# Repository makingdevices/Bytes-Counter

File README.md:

<!-- Improved compatibility of back to top link: See: https://github.com/othneildrew/Best-README-Template/pull/73 -->

<!--
*** Thanks for checking out the Best-README-Template. If you have a suggestion
*** that would make this better, please fork the repo and create a pull request
*** or simply open an issue with the tag "enhancement".
*** Don't forget to give the project a star!
*** Thanks again! Now go create something AMAZING! :D
-->

<!-- PROJECT SHIELDS -->
<!--
*** I'm using markdown "reference style" links for readability.
*** Reference links are enclosed in brackets [ ] instead of parentheses ( ).
*** See the bottom of this document for the declaration of the reference variables
*** for contributors-url, forks-url, etc. This is an optional, concise syntax you may use.
*** https://www.markdownguide.org/basic-syntax/#reference-style-links
-->
[![Instagram][ig-shield]][ig-url]
[![PCBWAY][sponsor-shield]][sponsor-url]
[![Stargazers][stars-shield]][stars-url]
[![Issues][issues-shield]][issues-url]
[![LinkedIn][linkedin-shield]][linkedin-url]

<!-- PROJECT LOGO -->
<br />
<div align="center">

<h3 align="center">Making Devices</h3>

  <p align="center">
    Open Source projects where we struggle with engineering, electronics, coding and who knows what else... In this case, Bytes Counter is a very simple digital tally counter, so hopefully you may find it interesting ;)
  </p>
</div>

<!-- TABLE OF CONTENTS -->
<details>
  <summary>Table of Contents</summary>
  <ol>
    <li>
      <a href="#about-the-project">About The Project</a>
      <ul>
        <li><a href="#built-with">Built With</a></li>
      </ul>
    </li>
    <li>
      <a href="#Build-one">Build one</a>
      <ul>
      </ul>
    </li>
    <li><a href="#usage">Usage</a></li>
    <li><a href="#roadmap">Roadmap</a></li>
    <li><a href="#license">License</a></li>
    <li><a href="#contact">Contact</a></li>
    <li><a href="#Sponsor">Sponsor</a></li>
  </ol>
</details>

<!-- ABOUT THE PROJECT -->
## About The Project

[![Bytes Counter Shot][product-screenshot]](https://makingdevices.com/Bytes-Counter)

Bytes Counter is a simple Tally Counter for counting people in places, helping you in inventories, practising soldering or just counting things at work! The project was chosen to test some PCB manufacturer capabilities and experiment with both the XLP (Extreme Low-Power Technology) and the pic18LF14k50 itself

The PCB does not have any power button, since the project's approach is to use the XLP technology of the PIC. It only has two buttons: increase/decrease the count.

A buzzer helps you count anything without needing to read the display every time so that you can focus on your work.

Even after weeks or months, the count is kept while in deep sleep mode.

<p align="right">(<a href="#readme-top">back to top</a>)</p>

### Built With

[![Microcontroller][PIC]][PIC-url]
[![MPLAB C][MPLAB-C]][MPLAB-C-url]
[![Kicad][kicad-shield]][kicad-url]
[![SPONSOR][sponsor-icon]][sponsor-url]

<p align="right">(<a href="#readme-top">back to top</a>)</p>

<!-- GETTING STARTED -->

## Build one

1. Get the gerber files for the latest version: [V1](https://github.com/makingdevices/Bytes-Counter/blob/main/v1/Gerber/BytesCounterV1.zip) 
2. Send them to a PCB manufacturer ([Our Sponsor is PCBWAY][sponsor-url])
3. Buy all the components from the [Bill Of Materials](https://github.com/makingdevices/Bytes-Counter/blob/main/v1/BytesCounter_BOM.xlsx)
4. Solder everything with the help of the [schematic](https://github.com/makingdevices/Bytes-Counter/blob/main/v1/schematicv1.pdf)
5. Burn the [latest firmware](https://github.com/makingdevices/Bytes-Counter/blob/main/v1/Simulation/Bytes_Counter.hex)
6. Give us a Star to the respository ;)

Here it is an assembly video:

[![Assembly Shot][YT-screenshot]](https://www.youtube.com/watch?v=Gu0cR_CFLYs)

<p align="right">(<a href="#readme-top">back to top</a>)</p>

<!-- USAGE EXAMPLES -->
## Usage

Instructions of use:

- Pressing "+" or "-" will increase/decrease the count.
- Long press "+" : Sound Event -> Activate/Deactivate buzzer sounds.
- Long press "-" : Reset event -> Reset the count.
- 60s without pressing any button: Deep Sleep Mode -> Display off.
- Any button pulsation will exit Deep Sleep Mode.

<p align="right">(<a href="#readme-top">back to top</a>)</p>

<!-- ROADMAP -->
## Roadmap

- [x] Count up/down and show it on screen
- [x] enable/disable sound when pressing buttons
- [x] Low Power Consumption
    - [x] Lower the frequency of the microcontroller at minimum
    - [x] Enter deep sleep mode automatically

See the [open issues](https://github.com/makingdevices/Bytes-Counter/issues) for a full list of proposed features (and known issues).

State: Project <b>FINISHED</b> - 01/08/2022

<p align="right">(<a href="#readme-top">back to top</a>)</p>

<!-- LICENSE -->
## License

Distributed under three licenses:
- [Hardware](/License/HW_cern_ohl_s_v2.pdf)
- [Software](/License/SW_GPLv3.0.txt)
- [Documentation](/License/Documentation_CC-BY-SA-4.0.txt)

[![GPL v3 License][license-shield]][license-url] 
<p align="right">(<a href="#readme-top">back to top</a>)</p>

<!-- CONTACT -->
## Contact

Making Devices - [@MakingDevices](https://www.instagram.com/makingdevices/)

Project Link: [https://github.com/makingdevices/Bytes-Counter](https://github.com/makingdevices/Bytes-Counter)

Other Links: [LinkTree](https://makingdevices.com/links/)

<p align="right">(<a href="#readme-top">back to top</a>)</p>

<!-- Sponsor -->
## Sponsor

[PCBWAY](https://www.pcbway.com/?from=makingdevices) helped us with the fabrication of the PCBs. You can check their quality with the following pictures:

[![PCB Shot 1][pcb_pic1]](https://www.pcbway.com/?from=makingdevices)
[![PCB Shot 2][pcb_pic2]](https://www.pcbway.com/?from=makingdevices)

Should you want to colaborate with MakingDevices, you can buy a [BytesCounter fully assembled and ready to use](https://www.pcbway.com/project/gifts_detail/Bytes_Counter_v1_0_4c88cb45.html) ;).

<p align="right">(<a href="#readme-top">back to top</a>)</p>

<!-- MARKDOWN LINKS & IMAGES -->
<!-- https://www.markdownguide.org/basic-syntax/#reference-style-links -->
[contributors-shield]: https://img.shields.io/github/contributors/makingdevices/Bytes-Counter.svg?style=for-the-badge
[contributors-url]: https://github.com/makingdevices/Bytes-Counter/graphs/contributors
[forks-shield]: https://img.shields.io/github/forks/makingdevices/Bytes-Counter.svg?style=for-the-badge
[forks-url]: https://github.com/makingdevices/Bytes-Counter/network/members
[stars-shield]: https://img.shields.io/github/stars/makingdevices/Bytes-Counter.svg?style=for-the-badge
[stars-url]: https://github.com/makingdevices/Bytes-Counter/stargazers
[issues-shield]: https://img.shields.io/github/issues/makingdevices/Bytes-Counter.svg?style=for-the-badge
[issues-url]: https://github.com/makingdevices/Bytes-Counter/issues
[license-shield]: /images/license.png
[license-url]: https://github.com/makingdevices/Bytes-Counter/tree/main/License
[linkedin-shield]: https://img.shields.io/badge/-LinkedIn-black.svg?style=for-the-badge&logo=linkedin&colorB=555
[linkedin-url]: https://www.linkedin.com/company/making-devices/
[sponsor-shield]: https://img.shields.io/badge/SPONSOR-PCBWAY-black.svg?style=for-the-badge&colorB=1200
[sponsor-url]: https://www.pcbway.com/?from=makingdevices
[sponsor-screenshot]: /images/PCB_sponsor.png
[product-screenshot]: images/screenshot.jpg
[pcb_pic1]: images/bytescounter_pcb_1.jpg
[pcb_pic2]: images/bytescounter_pcb_2.jpg
[PIC]: https://img.shields.io/badge/PIC18LF14K50-000000?style=for-the-badge
[PIC-url]: http://ww1.microchip.com/downloads/en/devicedoc/40001350f.pdf
[kicad-shield]: https://img.shields.io/badge/kicad-0b03fc?style=for-the-badge&logo=kicad&logoColor=white
[kicad-url]: https://www.kicad.org/
[YT-screenshot]: images/YT_assembly.PNG
[sponsor-icon]:  https://img.shields.io/badge/-PCBWAY-black.svg?style=for-the-badge&colorB=1200
[ig-shield]: https://img.shields.io/badge/instagram-a83297?style=for-the-badge&logo=instagram&logoColor=white
[ig-url]: https://www.instagram.com/makingdevices/
[MPLAB-C]: https://img.shields.io/badge/MPLAB%20C18-DD0031?style=for-the-badge&logo=C&logoColor=white
[MPLAB-C-url]: https://www.microchip.com/en-us/development-tool/SW006011
[Svelte.dev]: https://img.shields.io/badge/Svelte-4A4A55?style=for-the-badge&logo=svelte&logoColor=FF3E00
[Svelte-url]: https://svelte.dev/
[Laravel.com]: https://img.shields.io/badge/Laravel-FF2D20?style=for-the-badge&logo=laravel&logoColor=white
[Laravel-url]: https://laravel.com
[Bootstrap.com]: https://img.shields.io/badge/Bootstrap-563D7C?style=for-the-badge&logo=bootstrap&logoColor=white
[Bootstrap-url]: https://getbootstrap.com
[JQuery.com]: https://img.shields.io/badge/jQuery-0769AD?style=for-the-badge&logo=jquery&logoColor=white
[JQuery-url]: https://jquery.com

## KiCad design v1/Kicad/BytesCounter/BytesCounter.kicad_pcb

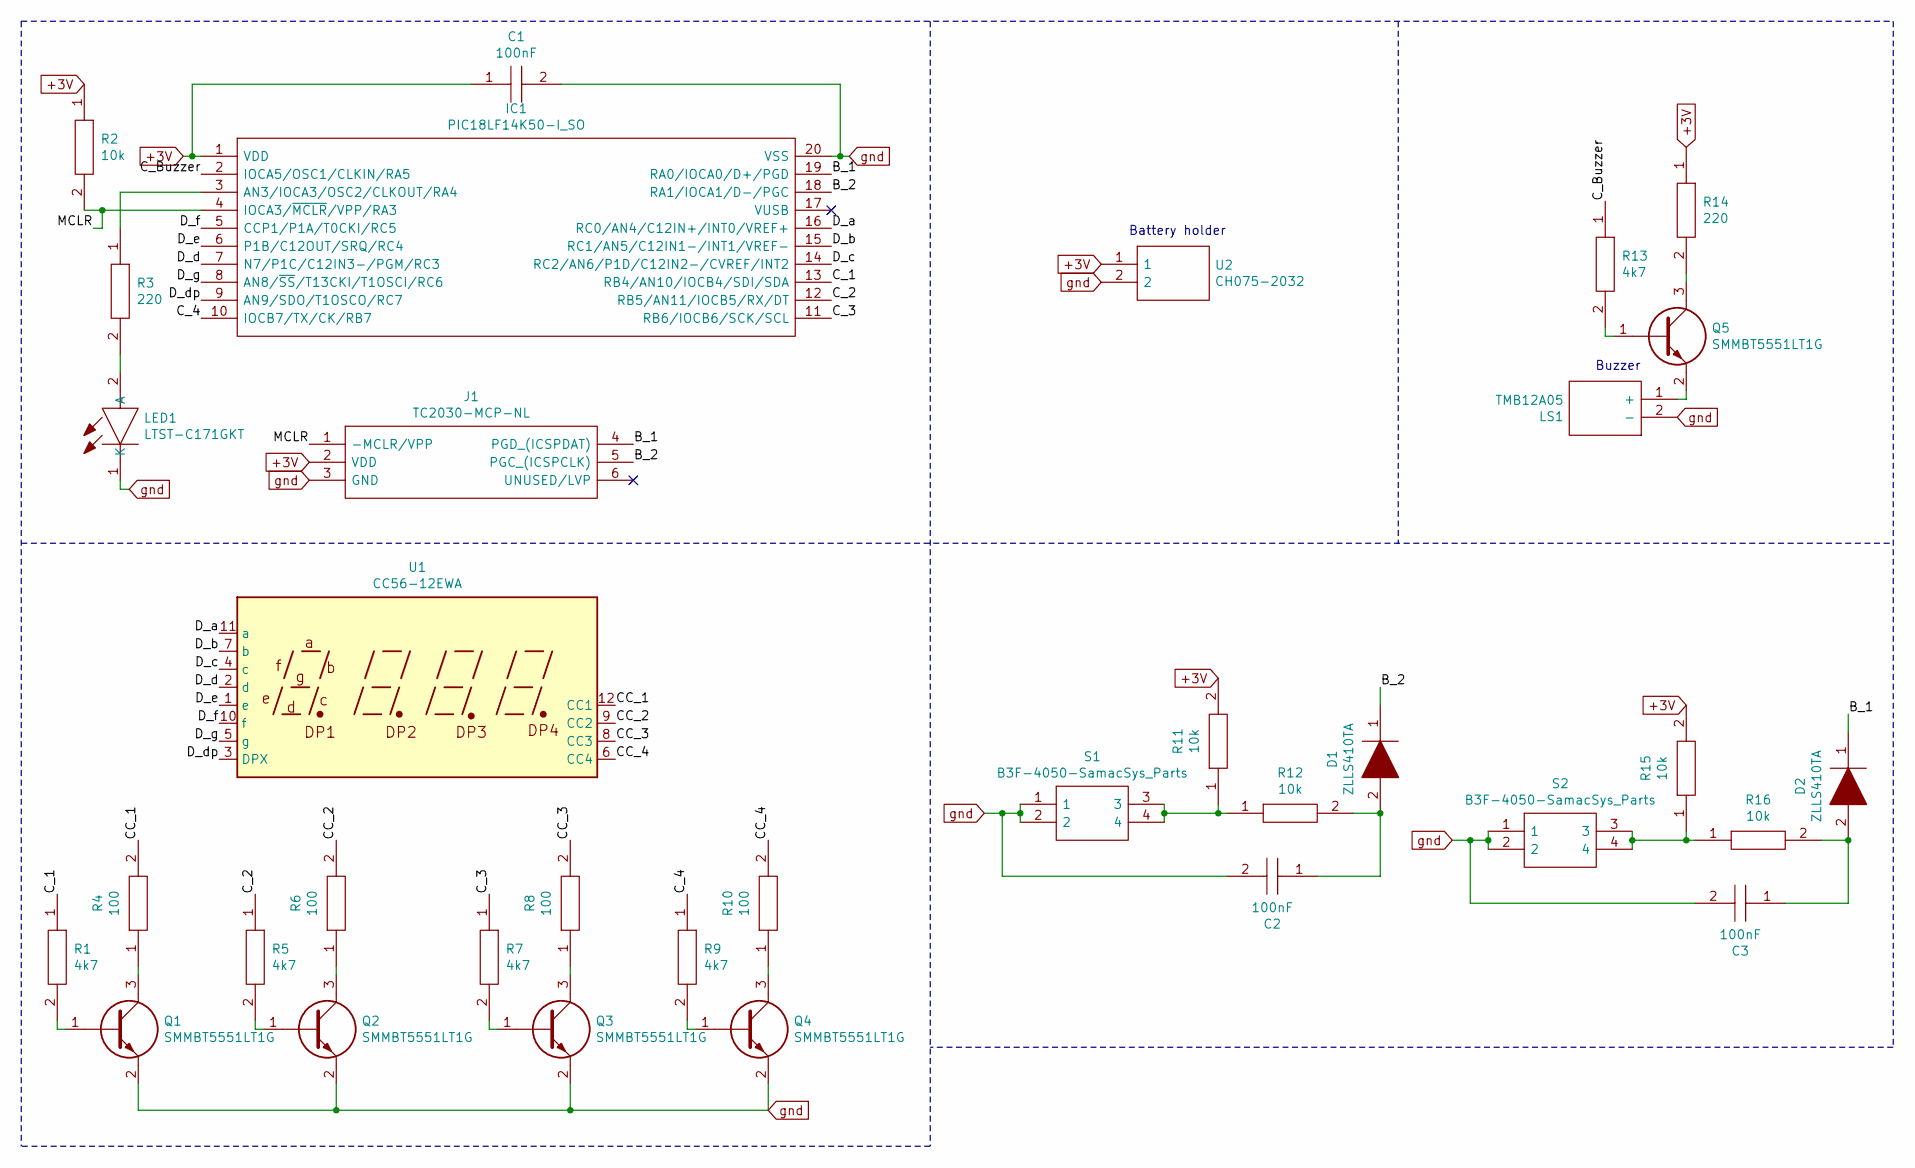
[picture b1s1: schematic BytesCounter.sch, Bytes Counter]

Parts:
C1, C2, C3: 100nF; CAPC2012X145N; Manufacturer_Part_Number GCG21BR71H154KA01K
D1, D2: ZLLS410TA; SOD2513X120N; Manufacturer_Part_Number ZLLS410TA
IC1: PIC18LF14K50-I_SO; SSOP-20_5.3x7.2mm_P0.65mm; Manufacturer_Part_Number PIC18LF14K50-I/SO
J1: TC2030-MCP-NL; Manufacturer_Part_Number TC2030-MCP-NL
LED1: LTST-C171GKT; LEDC2012X90N; Manufacturer_Part_Number LTST-C171GKT
LS1: TMB12A05; Manufacturer_Part_Number TMB12A05
Q1, Q2, Q3, Q4, Q5: SMMBT5551LT1G; SOT96P237X111-3N; Manufacturer_Part_Number SMMBT5551LT1G
R1, R5, R7, R9, R13: 4k7; RESC2012X65N; Manufacturer_Part_Number KTR10EZPF4220
R2, R11, R12, R15, R16: 10k; RESC2012X65N; Manufacturer_Part_Number KTR10EZPF4220
R3, R14: 220; RESC2012X65N; Manufacturer_Part_Number KTR10EZPF4220
R4, R6, R8, R10: 100; RESC2012X65N; Manufacturer_Part_Number KTR10EZPF4220
S1, S2: B3F-4050-SamacSys_Parts; B3F-4000; Manufacturer_Part_Number B3F-4050; Mouser Part Number 653-B3F-4050
U1: CC56-12EWA; CA56-12EWA
U2: CH075-2032; CH0752032; Manufacturer_Part_Number CH075-2032

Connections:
+3V: C1.1, IC1.1 (VDD), J1.2 (VDD), R2.1, R11.2, R14.1, R15.2, U2.1
/B_1: D2.1, IC1.19 (RA0/IOCA0/D+/PGD), J1.4 (PGD_(ICSPDAT))
/B_2: D1.1, IC1.18 (RA1/IOCA1/D-/PGC), J1.5 (PGC_(ICSPCLK))
/CC_1: R4.2, U1.12 (CC1)
/CC_2: R6.2, U1.9 (CC2)
/CC_3: R8.2, U1.8 (CC3)
/CC_4: R10.2, U1.6 (CC4)
/C_1: IC1.13 (RB4/AN10/IOCB4/SDI/SDA), R1.1
/C_2: IC1.12 (RB5/AN11/IOCB5/RX/DT), R5.1
/C_3: IC1.11 (RB6/IOCB6/SCK/SCL), R7.1
/C_4: IC1.10 (IOCB7/TX/CK/RB7), R9.1
/C_Buzzer: IC1.2 (IOCA5/OSC1/CLKIN/RA5), R13.1
/D_a: IC1.16 (RC0/AN4/C12IN+/INT0/VREF+), U1.11 (a)
/D_b: IC1.15 (RC1/AN5/C12IN1-/INT1/VREF-), U1.7 (b)
/D_c: IC1.14 (RC2/AN6/P1D/C12IN2-/CVREF/INT2), U1.4 (c)
/D_d: IC1.7 (N7/P1C/C12IN3-/PGM/RC3), U1.2 (d)
/D_dp: IC1.9 (AN9/SDO/T1OSCO/RC7), U1.3 (DPX)
/D_e: IC1.6 (P1B/C12OUT/SRQ/RC4), U1.1 (e)
/D_f: IC1.5 (CCP1/P1A/T0CKI/RC5), U1.10 (f)
/D_g: IC1.8 (AN8/~SS~/T13CKI/T1OSCI/RC6), U1.5 (g)
/MCLR: IC1.4 (IOCA3/~MCLR~/VPP/RA3), J1.1 (-MCLR/VPP), R2.2
unnamed: C2.1, D1.2, R12.2
unnamed: C3.1, D2.2, R16.2
unnamed: IC1.3 (AN3/IOCA3/OSC2/CLKOUT/RA4), R3.1
unnamed: LED1.2 (A), R3.2
unnamed: LS1.1 (+), Q5.2
unnamed: Q1.1, R1.2
unnamed: Q1.3, R4.1
unnamed: Q2.1, R5.2
unnamed: Q2.3, R6.1
unnamed: Q3.1, R7.2
unnamed: Q3.3, R8.1
unnamed: Q4.1, R9.2
unnamed: Q4.3, R10.1
unnamed: Q5.1, R13.2
unnamed: Q5.3, R14.2
unnamed: R11.1, R12.1, S1.3, S1.4
unnamed: R15.1, R16.1, S2.3, S2.4
gnd: C1.2, C2.2, C3.2, IC1.20 (VSS), J1.3 (GND), LED1.1 (K), LS1.2 (-), Q1.2, Q2.2, Q3.2, Q4.2, S1.1, S1.2, S2.1, S2.2, U2.2

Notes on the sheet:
Battery holder
Buzzer

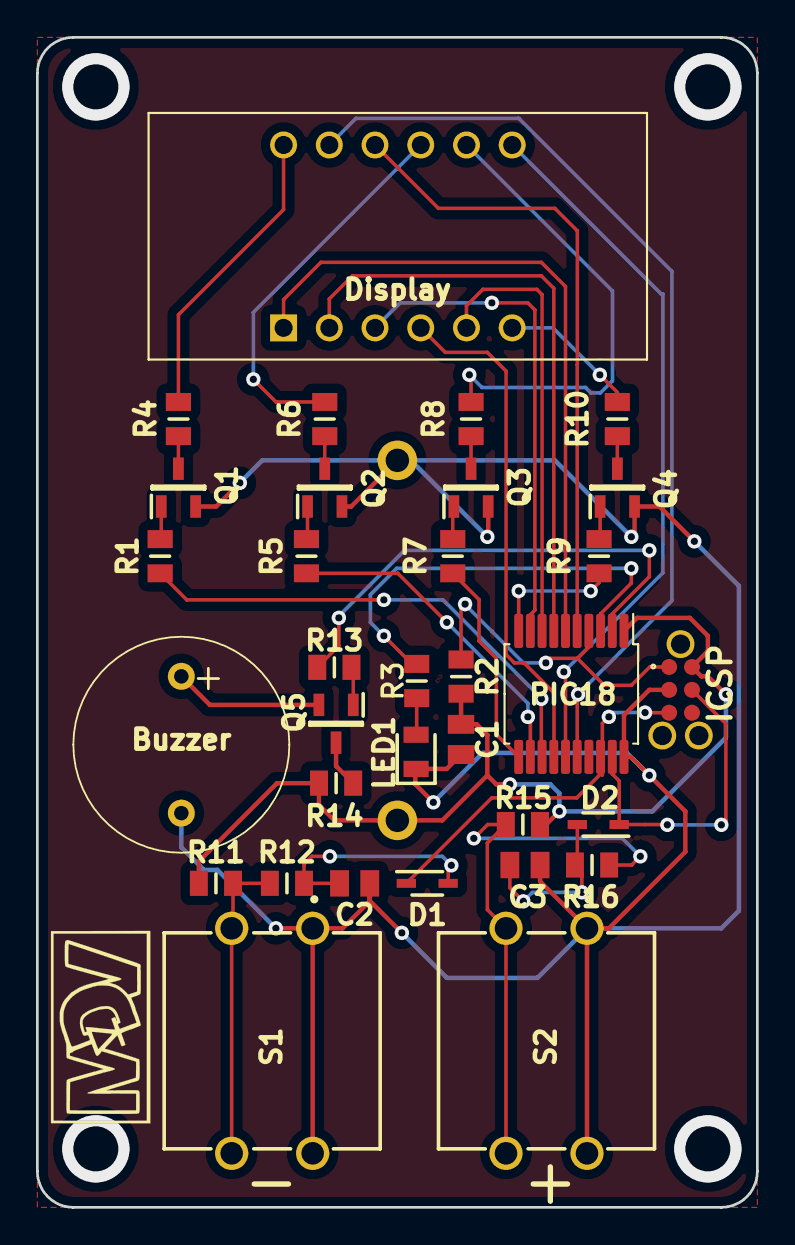
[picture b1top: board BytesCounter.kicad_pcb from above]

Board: 2 copper layers, 40.0 x 65.0 mm, 34 parts (1 on the bottom side), 39 nets.

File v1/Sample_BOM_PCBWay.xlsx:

|  |  |  | Bytes Counter v1 BOM (Sample Bill of Materials)
Item # | *Designator | *Qty | Layer | Manufacturer | *Mfg Part # | Description / Value | *Package/Footprint | Type | Your Instructions / Notes | Price
1 | IC1 | 1 | top | Microchip | PIC18LF14K50T-I/SS | MicroProcessor | 20-SSOP | SMD | It has to be the official part
2 | LED1 | 1 | top | TOGIALED | TJ-S2012SW8TGLC2G-A5 | Green LED | 0805 | SMD | It can be replaced for other parts
3 | Q1,Q2,Q3,Q4,Q5 | 5 | top | TOSHIBA | 2SC2712 | NPN transistor 150mA | SOT23-3 | SMD | It can be replaced for other parts
4 | R3, R14 | 2 | top | RALEC | RTT052200FTP | 220 Ohm Resistor / 125mW | 0805 | SMD | It can be replaced for other parts
5 | R4, R6, R8, R10 | 4 | top | YAGEO | RC0805FR-7W100RL | 100 Ohm Resistor / 250mW | 0805 | SMD | It can be replaced for other parts
6 | R1, R5, R7, R9, R13 | 5 | top | RALEC | RTT054701FTP | 4.7k Ohm Resistor / 125mW | 0805 | SMD | It can be replaced for other parts
7 | R2, R11, R12, R15, R16 | 5 | top | YAGEO | RT0805CRD0710KL | 10K Ohm Resistor / 125mW | 0805 | SMD | It can be replaced for other parts
8 | C1, C2, C3 | 3 | top | YAGEO | AC0805KRX7R9BB104 | 100nF Capacitor 50V | 0805 | SMD | It can be replaced for other parts
9 | D1, D2 | 2 | top | BAS170WS-E3-08 | Vishay Intertech | 70V Schottky diode | SOD-323-2 | SMD | It can be replaced for other parts
10 | S1, S2 | 2 | top | Diptronics | DTS-21K-V | Buttons | 4POS | thru-hole | It can be replaced for other parts
11 | U2 | 1 | Bottom | AAA-BAT-029-K01 | LOTES | 2032 Battery Holder | 2POS | thru-hole | It can be replaced for other parts
12 | U1 | 1 | top | FJ3461AH | Shenzhen Zhihao Elec | Display | 12POS | thru-hole | It can be replaced for other parts
13 | LS1 | 1 | top | Jiangsu Huaneng Elec | TMB12A05 | Buzzer | 2POS | thru-hole | It can be replaced for other parts
 | Total: | 33 |  |  |  |  |  |  | Total:

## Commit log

2022-08-06 Project Finished
2022-08-06 Readme
2022-08-06 updating readme
2022-08-15 New files
    Schematic
2022-08-20 new license
2022-08-20 update license
2022-08-29 Recover
2022-12-19 update folders
2023-01-06 no message
